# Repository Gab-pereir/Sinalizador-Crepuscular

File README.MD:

# Sinalizador Crepuscular Automatizado

Seja bem vindo a esse repositório dedicado ao desenvolvimento de um Sinalizador Crepuscular Automatizado. Este projeto tem como objetivo confeccionar uma placa de circuito impresso para um sistema inovador de iluminação em transições entre dia e noite

## Descrição

O sinalizador Crepuscular utiliza tecnologia avançada para detectar mudanças na luz ambiente, proporcionando iluminação eficiente e personalizada durante as diferentes fases do dia

## Clonar o Repositório e Abrir no KiCad

Se você deseja explorar ou contribuir para o projeto do Sinalizador Crepuscular, siga os passos abaixo para clonar o repositório e abrir o projeto no KiCad:

### 1. Faça um Fork do Repositório

- No canto superior direito desta página, clique no botão "Fork" para criar uma cópia do repositório no seu próprio perfil.

### 2. Clone o Repositório

- Abra o terminal no seu sistema.

- Utilize o seguinte comando para clonar o repositório para o seu ambiente local 

  ```bash
  git clone https://github.com/Gab-pereir/Sinalizador-Crepuscular.git

### 3. Abra o Projeto no KiCad

- Abra o KiCad.

- Vá para "File" > "Open Project".

- Navegue até o diretório do projeto clonado.

- Escolha o arquivo de projeto correspondente à placa desejada 

## Organização das Pastas

```Sinalizador-Crepuscular/
|-- fonte/
|   |-- docs/
|   |   |-- Especificações elétricas da Placa da Fonte
|   |
|   |-- gerbers/
|   |   |-- Arquivos Gerber relacionados à Placa da Fonte
|   |
|   |-- OutrosDocumentos/
|       |-- Outros documentos relevantes para a Placa da Fonte
|
|-- haste_superior/
|   |-- docs/
|   |   |-- Especificações elétricas da Haste Superior
|   |
|   |-- gerbers/
|   |   |-- Arquivos Gerber relacionados à Haste Superior
|   |
|   |-- OutrosDocumentos/
|       |-- Outros documentos relevantes para a Haste Superior
|
|-- logica_de_comando/
|   |-- docs/
|   |   |-- Especificações elétricas da Lógica de Comando
|   |
|   |-- gerbers/
|   |   |-- Arquivos Gerber relacionados à Lógica de Comando
|   |
|   |-- OutrosDocumentos/
        |-- Outros documentos relevantes para a Lógica de Comando

```

## Contribuindo

Sinta-se à vontade para contribuir para o desenvolvimento do Sinalizador Crepuscular Automatizado.

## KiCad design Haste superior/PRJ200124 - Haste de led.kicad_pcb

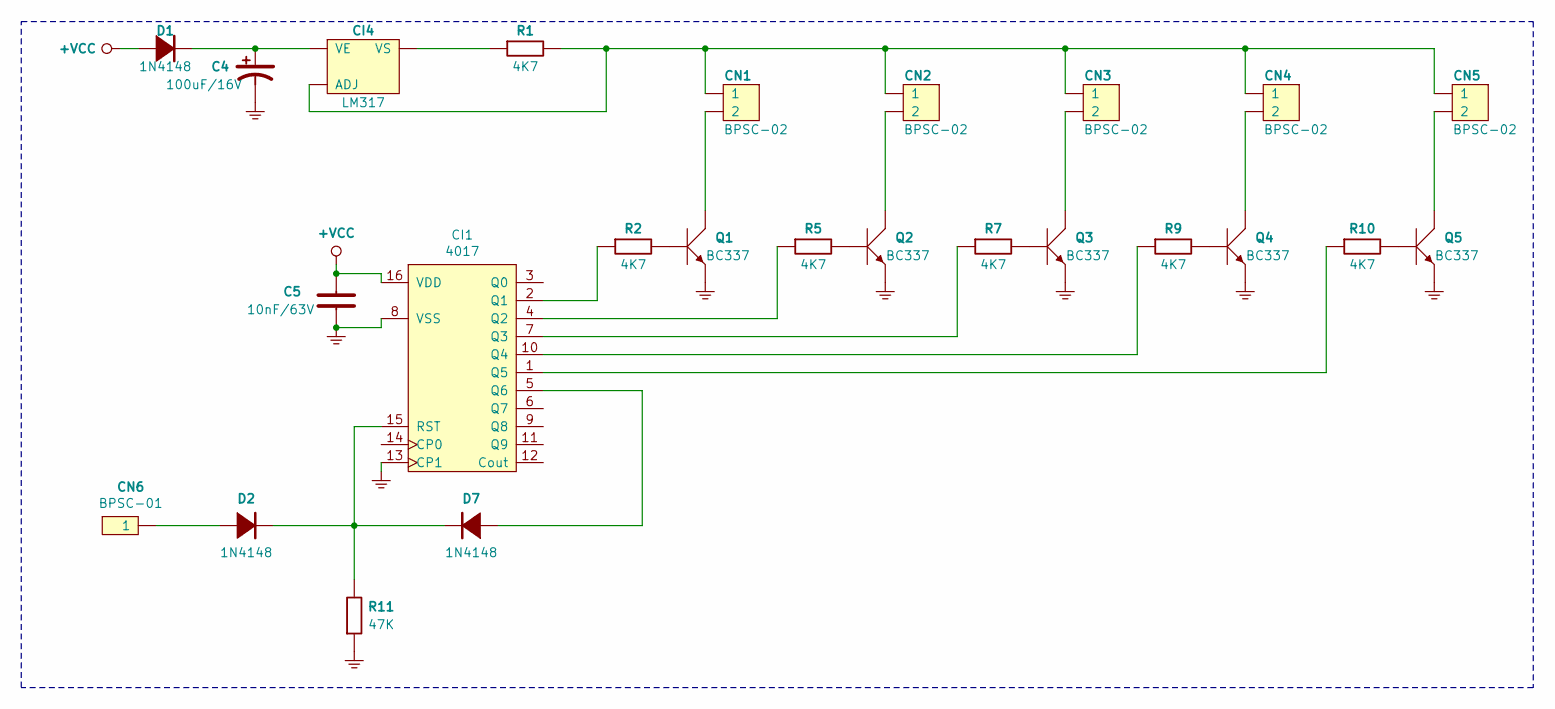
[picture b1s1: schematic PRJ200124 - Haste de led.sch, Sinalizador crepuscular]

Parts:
C4: 100uF(16V)-Panasonic(FCA); Capacitor(Eletrolitico)-Radial(6.3x11.0)mm-(Azul_Marinho); Part Number Part Number
C5: 10nF(63V)-TDK(B32529)-(10%); Capacitor(MKT)-TDK(B32529)-(7.3x2.5x6.5)mm; Part Number B32529C0103K
CI1: CD4017BE; PDIP016N; Part Number CD4017BE
CI4: LM317BTG(180); TO220-3(180); Part Number LM317BTG
CN1, CN2, CN3, CN4, CN5: BPSC-02(Metaltex-BP); BPSC-02; Part Number BPSC-02
CN6: BPSC-01(Metaltex-BP); BPSC-01; Part Number BPSC-01
D1, D2, D7: 1N4148; DO-35(Vidro-Vermelho); Part Number Part Number
Q1, Q2, Q3, Q4, Q5: BC337; TO92-3(Bent-Lead); Part Number BC337
R1, R2, R5, R7, R9, R10, R11: CFR12-(5%); CFR12-(5p); Part Number Part Number

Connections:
+VCC: C5.2, CI1.16 (VDD), D1.2 (A)
GND: C4.2, C5.1, CI1.8 (VSS), CI1.13 (CP1), Q1.3 (E), Q2.3 (E), Q3.3 (E), Q4.3 (E), Q5.3 (E), R11.1 (A)
unnamed: C4.1, CI4.3 (VE), D1.1 (K)
unnamed: CI4.1 (ADJ), CN1.1, CN2.1, CN3.1, CN4.1, CN5.1, R1.2 (B)
unnamed: CI4.2 (VS), R1.1 (A)
unnamed: CI1.1 (Q5), R10.1 (A)
unnamed: CI1.2 (Q1), R2.1 (A)
unnamed: CI1.4 (Q2), R5.1 (A)
unnamed: CI1.5 (Q6), D7.2 (A)
unnamed: CI1.7 (Q3), R7.1 (A)
unnamed: CI1.10 (Q4), R9.1 (A)
unnamed: CI1.15 (RST), D2.1 (K), D7.1 (K), R11.2 (B)
unnamed: CN1.2, Q1.1 (C)
unnamed: CN2.2, Q2.1 (C)
unnamed: CN3.2, Q3.1 (C)
unnamed: CN4.2, Q4.1 (C)
unnamed: CN5.2, Q5.1 (C)
unnamed: CN6.1, D2.2 (A)
unnamed: Q1.2 (B), R2.2 (B)
unnamed: Q2.2 (B), R5.2 (B)
unnamed: Q3.2 (B), R7.2 (B)
unnamed: Q4.2 (B), R9.2 (B)
unnamed: Q5.2 (B), R10.2 (B)

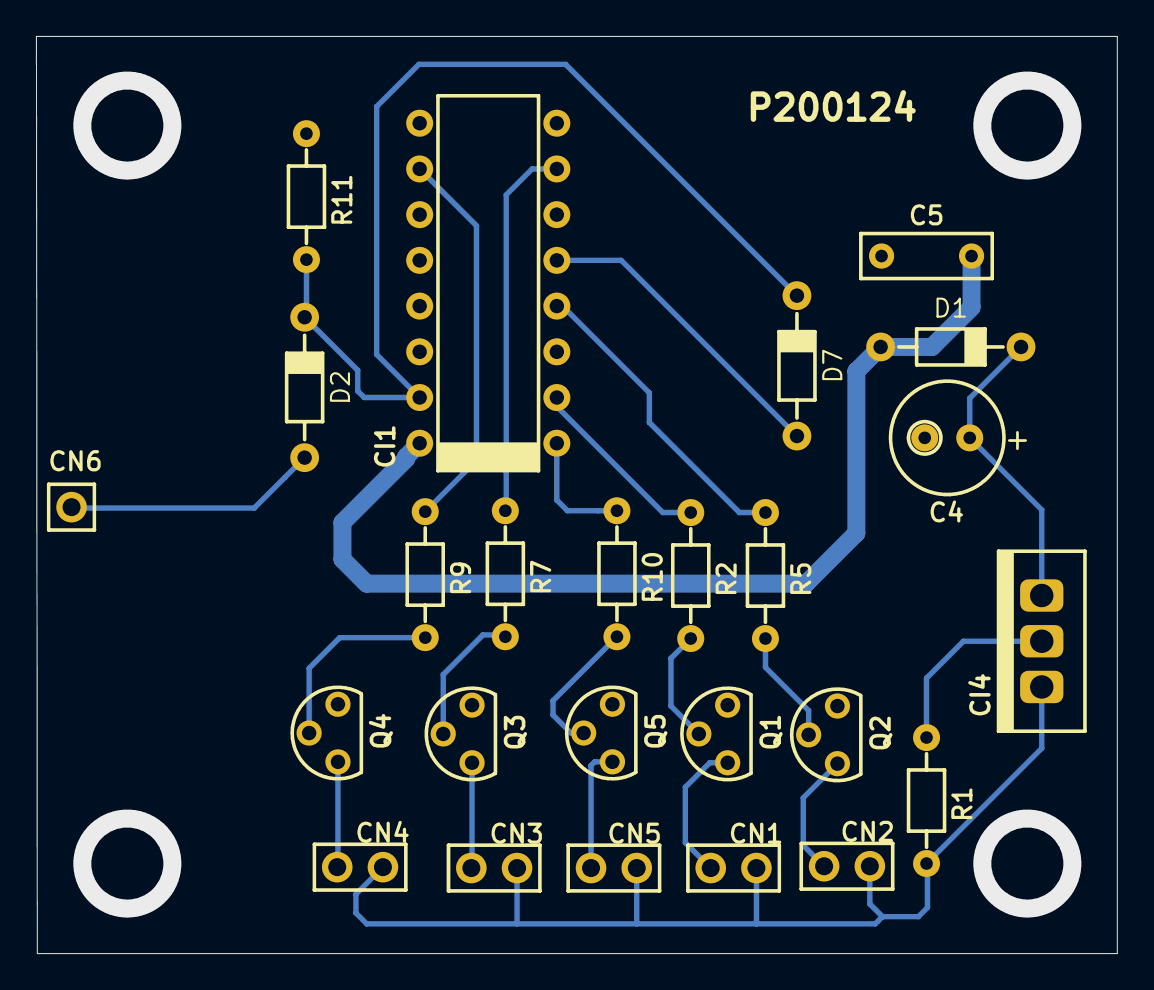
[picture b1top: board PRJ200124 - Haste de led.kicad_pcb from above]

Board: 2 copper layers, 60.0 x 51.0 mm, 25 parts (0 on the bottom side), 23 nets.

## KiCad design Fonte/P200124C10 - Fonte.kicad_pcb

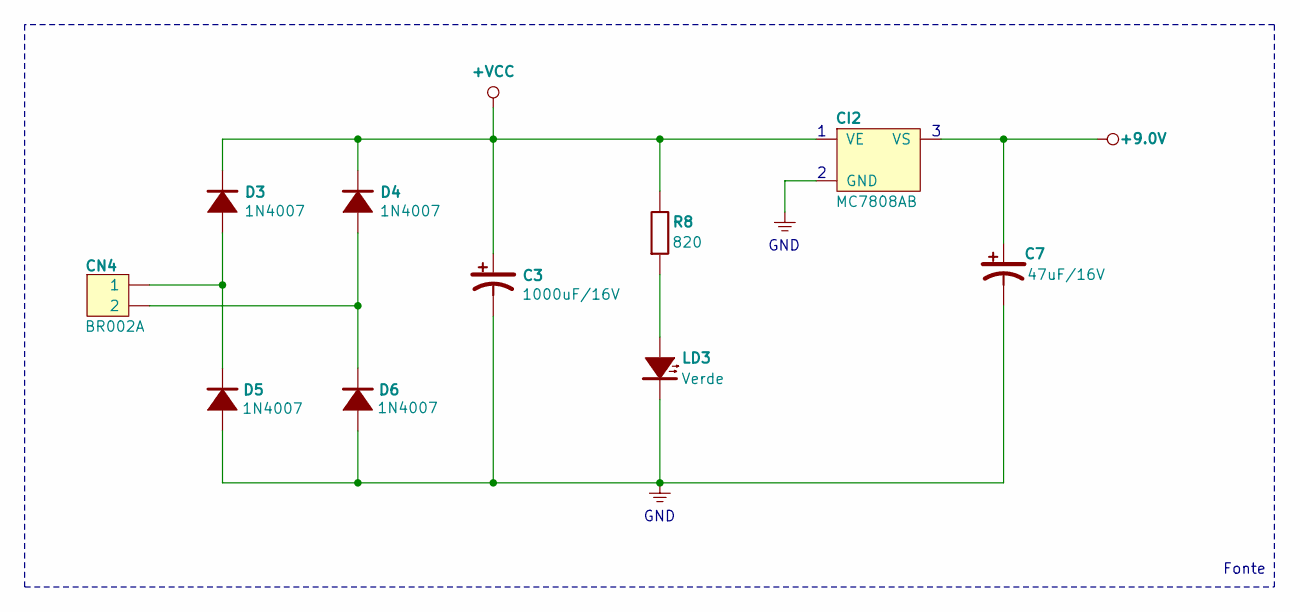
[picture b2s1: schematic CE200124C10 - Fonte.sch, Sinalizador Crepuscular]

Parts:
C3: 1000uF(16V)-Panasonic(FCA); Capacitor(Eletrolitico)-Radial(10.0x25.0)mm-(Azul_Marinho); Part Number Part Number
C7: 47uF(16V)-Panasonic(FCA); Capacitor(Eletrolitico)-Radial(5.0x11.0)mm-(Azul_Marinho); Part Number Part Number
CI2: MC7808B-(180); TO220-3(180); Part Number MC7808BTG
CN4: BR002A(Metaltex-BR0); BR002A-(Metaltex-BR0); Part Number BR002A
D3, D4, D5, D6: 1N4007; DO-41(Plastico); Part Number Part Number
LD3: Led-Redondo(3.0mm)-Pth-Verde(Difuso); Led(Pth)-Redondo(3.0mm)-Verde(Difuso); Part Number *
R8: CFR12-(5%); CFR12-(5p); Part Number Part Number

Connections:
+9.0V: C7.1, CI2.3 (VS)
+VCC: C3.1, CI2.1 (VE), D3.1 (K), D4.1 (K), R8.2 (B)
GND: C3.2, C7.2, CI2.2 (GND), D5.2 (A), D6.2 (A), LD3.1 (K)
unnamed: CN4.1, D3.2 (A), D5.1 (K)
unnamed: CN4.2, D4.2 (A), D6.1 (K)
unnamed: LD3.2 (A), R8.1 (A)

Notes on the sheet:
Fonte
GND

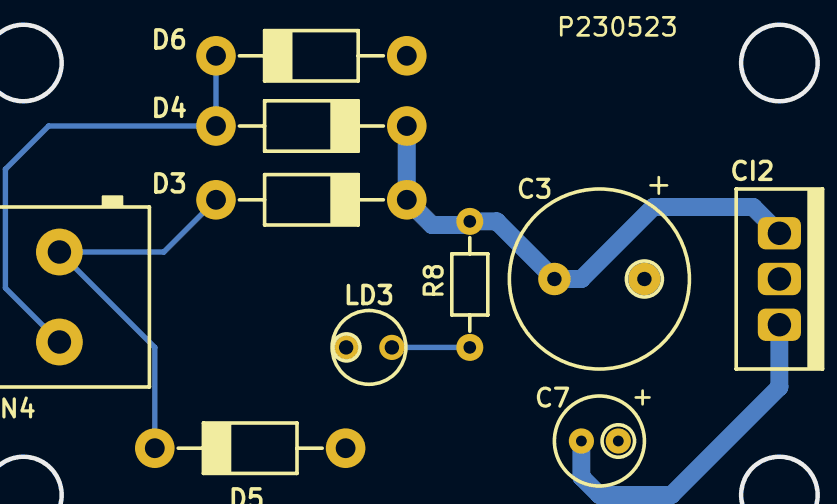
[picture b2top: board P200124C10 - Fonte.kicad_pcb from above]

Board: 2 copper layers, 10 parts (0 on the bottom side), 6 nets.

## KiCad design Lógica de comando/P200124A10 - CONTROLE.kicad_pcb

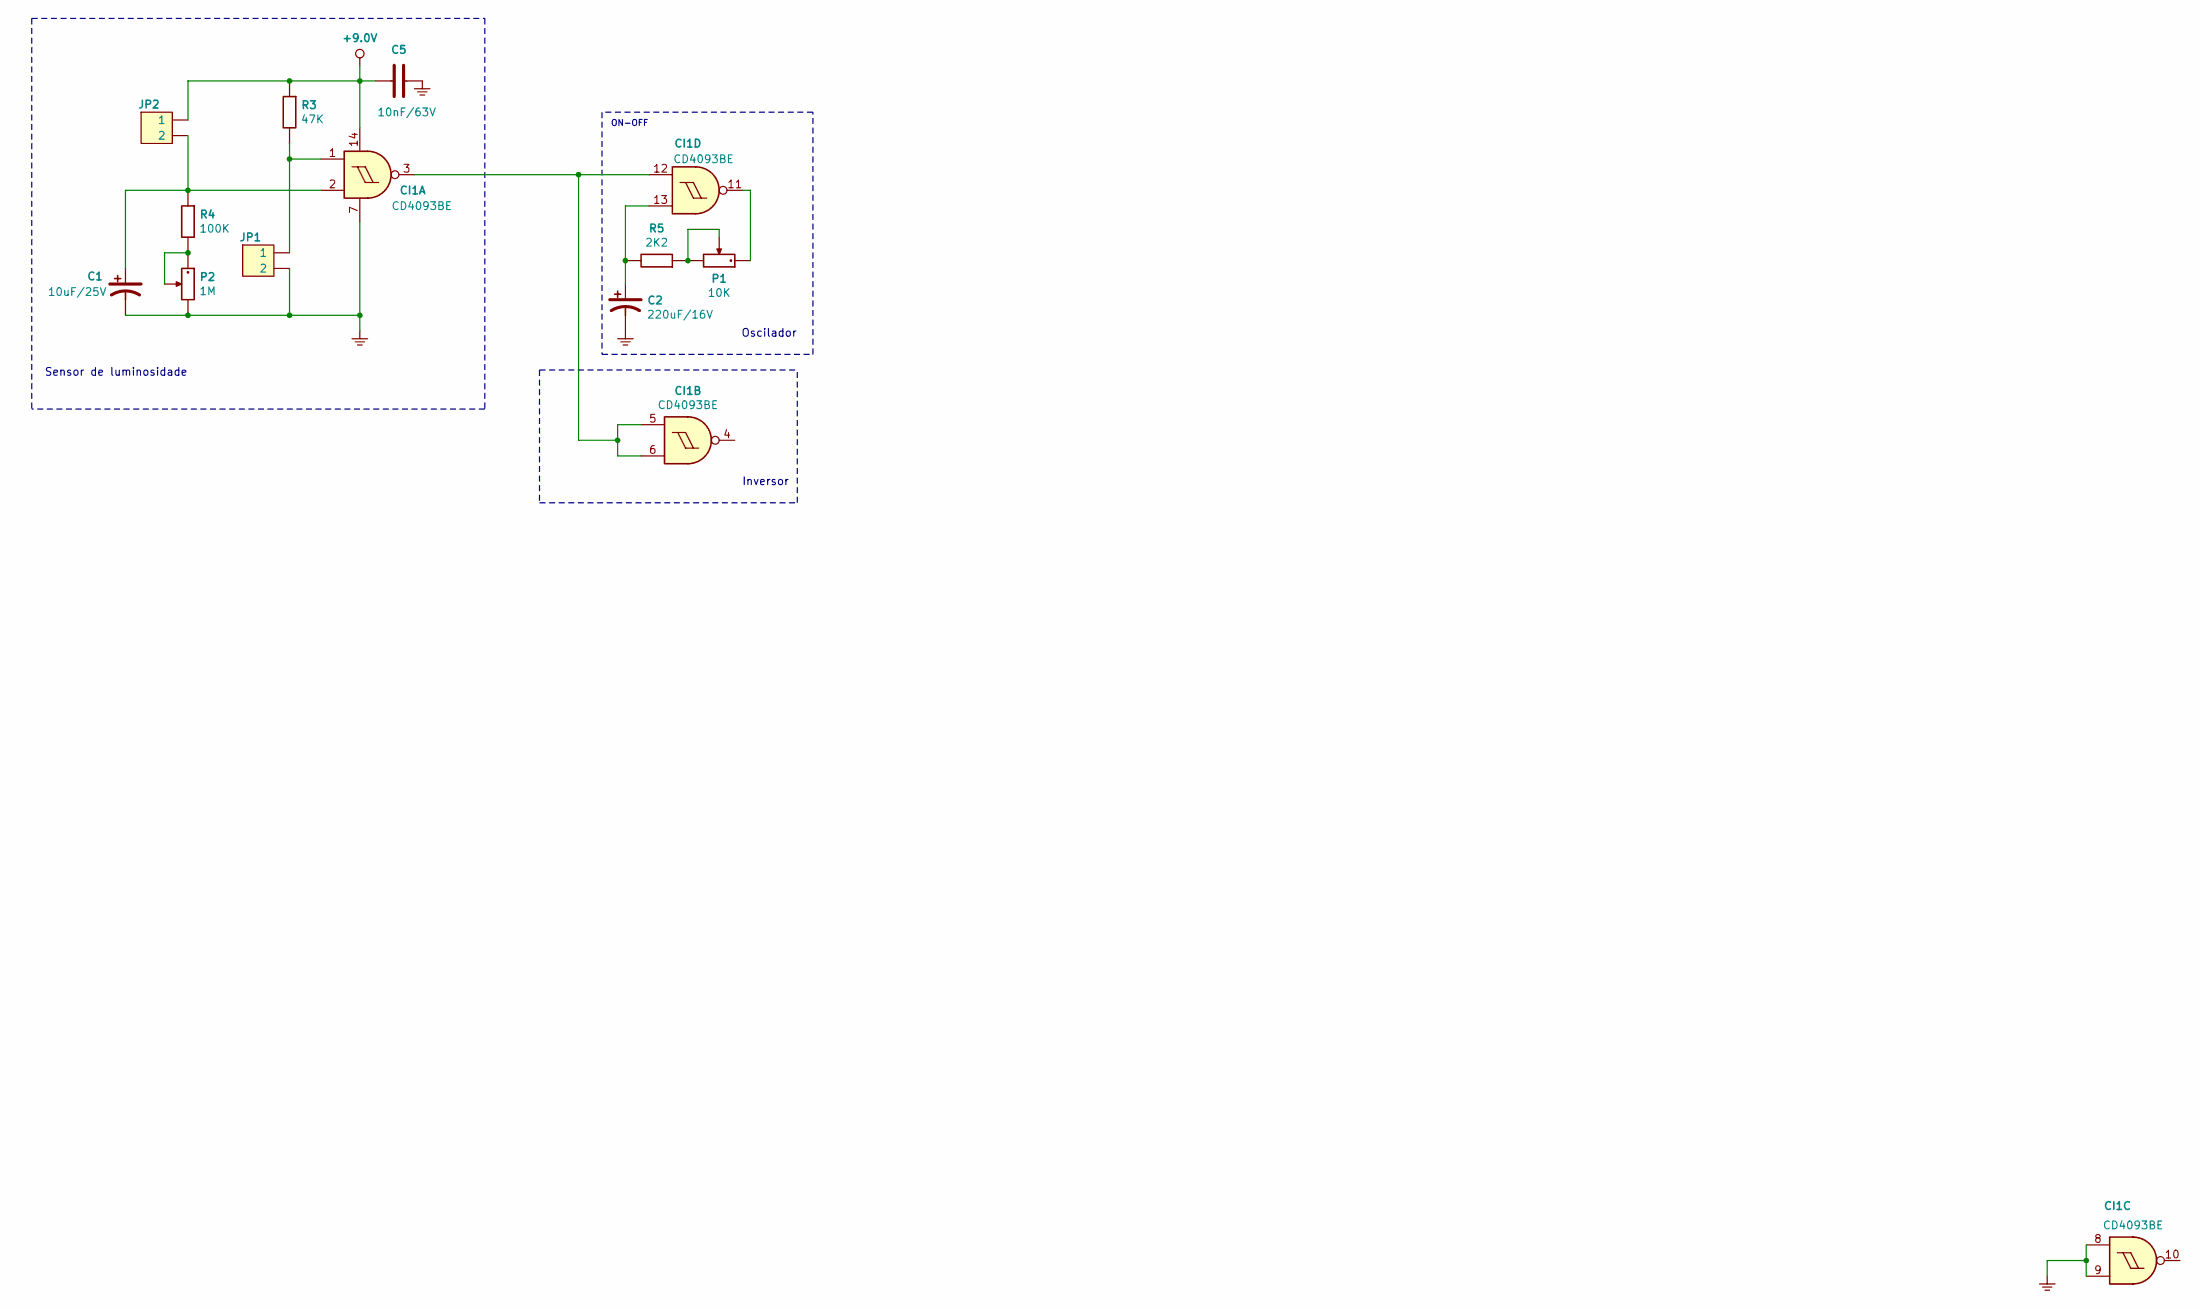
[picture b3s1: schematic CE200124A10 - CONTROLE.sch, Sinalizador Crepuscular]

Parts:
C1: 10uF(25V)-Panasonic(FCA); Capacitor(Eletrolitico)-Radial(4.0x7.0)mm-(Azul_Marinho); Part Number EEAFC1E100
C2: 220uF(16V)-Panasonic(FCA); Capacitor(Eletrolitico)-Radial(8.0x11.5)mm-(Azul_Marinho); Part Number Part Number
C5: 10nF(63V)-TDK(B32529)-(10%); Capacitor(MKT)-TDK(B32529)-(7.3x2.5x6.5)mm; Part Number B32529C0103K
CI1: CD4093BE; PDIP014N; Part Number CD4093BE
JP1, JP2: BPSC-02(Metaltex-BP); BPSC-02; Part Number BPSC-02
P1: 10K-Bourns(3386-F); TRIMPOT-Bourns(3386-F); Part Number 3386F-1-103
P2: 1M-Bourns(3386-F); TRIMPOT-Bourns(3386-F); Part Number 3386F-1-105
R3, R4, R5: CFR12-(5%); CFR12-(5p); Part Number Part Number

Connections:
+9.0V: C5.1, CI1.14 (VDD), JP2.1, R3.1 (A)
GND: C1.2, C2.2, C5.2, CI1.7 (VSS), CI1.8 (A3), CI1.9 (B3), JP1.2, P2.3
unnamed: C1.1, CI1.2 (B1), JP2.2, R4.1 (A)
unnamed: C2.1, CI1.13 (B4), R5.2 (B)
unnamed: CI1.1 (A1), JP1.1, R3.2 (B)
unnamed: CI1.11 (S4), P1.1
unnamed: CI1.3 (S1), CI1.5 (A2), CI1.6 (B2), CI1.12 (A4)
unnamed: P1.2, P1.3, R5.1 (A)
unnamed: P2.1, P2.2, R4.2 (B)

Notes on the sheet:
Sensor de luminosidade
Inversor
ON-OFF
Oscilador

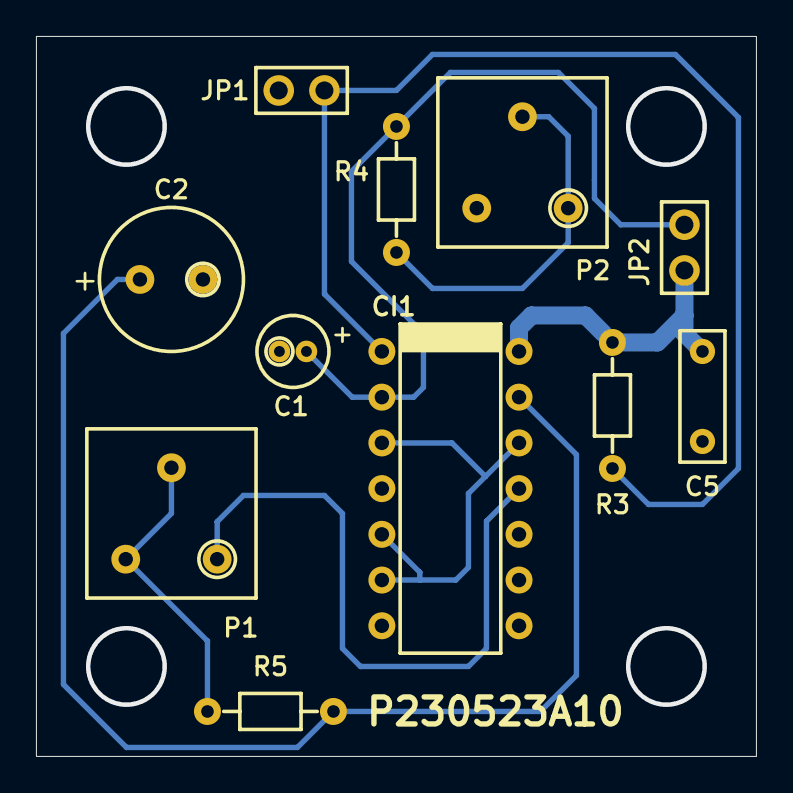
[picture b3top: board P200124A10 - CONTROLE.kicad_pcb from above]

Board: 2 copper layers, 40.0 x 40.0 mm, 11 parts (0 on the bottom side), 9 nets.

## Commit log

2024-01-20 📁 Adicionando a estrutura básica do projeto - Closes #1
2024-01-20 ✨ Implementação da lógica de comando - fixes #2
2024-01-20 ✨ Implementação do circuito impresso da fonte de alimentação - Fixes #3
2024-01-21 💡 Criação do circuito impresso da haste de leds - Closes #4
2024-01-22 📄 Atualização da documentação do projeto e inclusão do arquivo README - Closes #5
